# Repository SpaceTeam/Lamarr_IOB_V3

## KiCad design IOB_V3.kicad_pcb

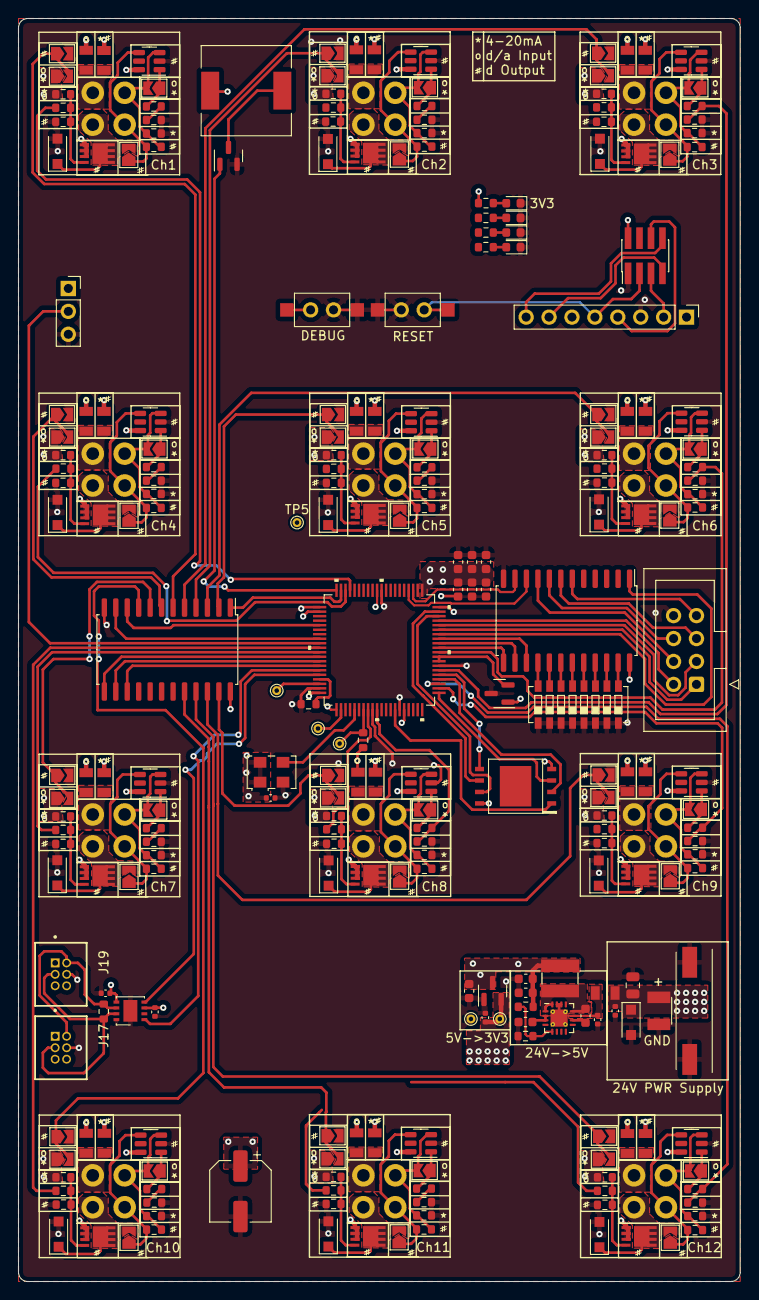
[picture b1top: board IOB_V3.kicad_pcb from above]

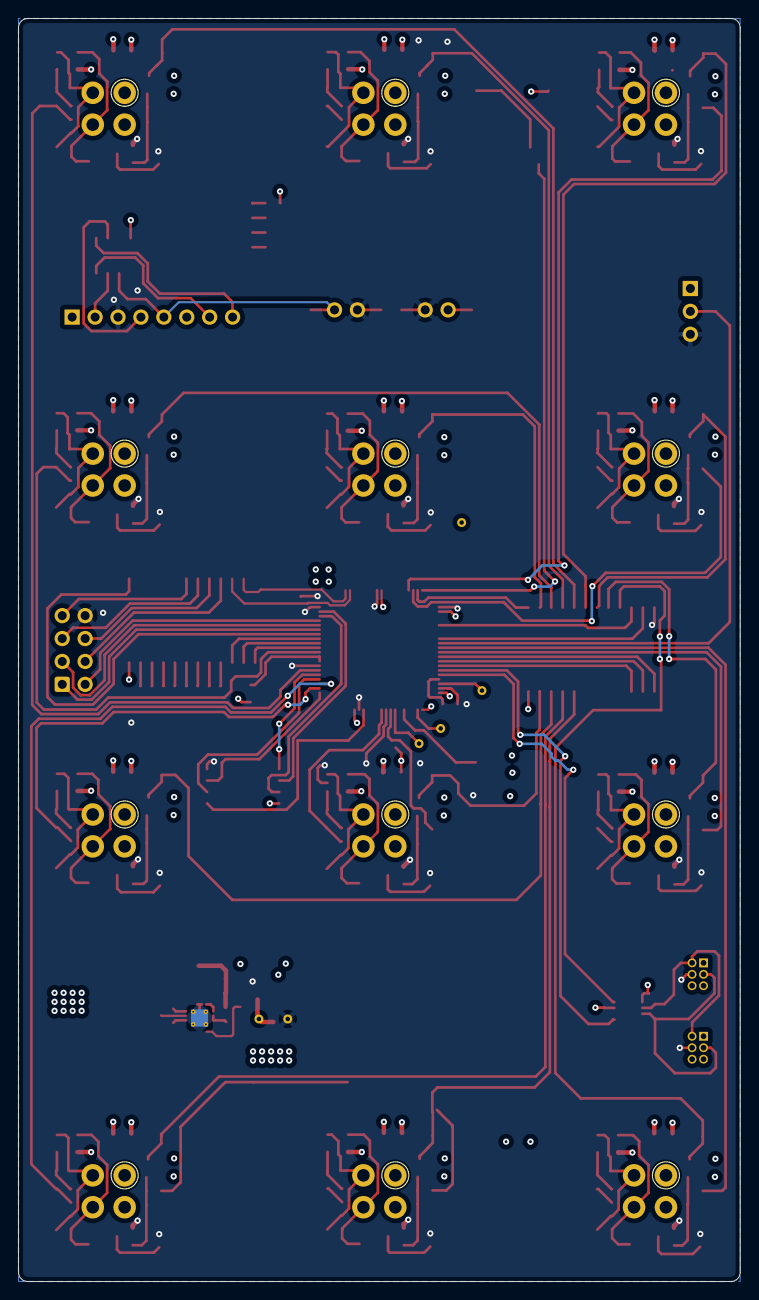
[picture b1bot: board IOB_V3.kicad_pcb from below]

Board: 4 copper layers, 80.0 x 140.0 mm, 266 parts (12 on the bottom side), 175 nets.

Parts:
C1, C3, C10, C11, C13, C15: 100n; C_0402_1005Metric
C2: 22u; C_0805_2012Metric
C4, C8: 10u; C_0603_1608Metric
C5, C9, C12, C16, C17, C18: 100n; C_0603_1608Metric
C6, C7: 22u; C_0603_1608Metric
C14: NP; CP_Elec_6.3x4.9
C19: 4.7u; C_0603_1608Metric
D1: 30V; D_SOD-123F
D2, D3, D4, D5, D6, D7, D8, D9, D10, D11, D12, D13: D; D_SOD-123F
D14, D15, D16, D17: LED; LED_0603_1608Metric
F1, F2, F3, F4, F5, F6, F7, F8, F9, F10, F11, F12, F13, F14, F15, F16, F17, F18, F19, F20, F21, F22, F23, F24, F25: Polyfuse; 0805L110SL PPTC Polyfuse Littelfuse
J1: Conn_01x02; Molex_MicroFit_2Pin_Vertical
J2: Conn_01x03; PinSocket_1x03_P2.54mm_Vertical
J3, J4, J5, J6, J7, J8, J9, J10, J11, J12, J13, J14: Conn_01x04; TE_M12_4_Pin_PCB
J15: Conn_01x08; PinHeader_1x08_P2.54mm_Vertical
J16: Conn_02x04_Odd_Even; PinHeader_2x04_P1.27mm_Vertical_SMD
J17, J19: TFC-103-01-F-D; SAMTEC_TFC-103-01-F-D
J18: Conn_01x08; IDC-Header_2x04_P2.54mm_Vertical
JP1, JP2, JP5, JP6, JP7, JP8, JP11, JP12, JP13, JP14, JP17, JP18, JP19, JP20, JP23, JP24, JP25, JP26, JP29, JP30, JP31, JP32, JP35, JP36, JP37, JP38, JP41, JP42, JP43, JP44, JP47, JP48, JP49, JP50, JP53, JP54, JP55, JP56, JP59, JP60, JP61, JP62, JP65, JP66, JP67, JP68, JP71, JP72: Jumper_2_Open; SolderJumper-2_P1.3mm_Open_TrianglePad1.0x1.5mm
L1: 4.7uH; SRN4018TA-4R7M
LS1: Speaker_Crystal; Piezo_Buzzer
Q1, Q2, Q3, Q4, Q5, Q6, Q7, Q8, Q9, Q10, Q11, Q12: BSZ0902NSATMA1; PG_TSDSON-8
Q13: SI2300; SOT-23
R1, R8, R15, R22, R29, R36, R43, R50, R57, R64, R71, R78, R93: 0R; R_0603_1608Metric
R2, R9, R16, R23, R30, R37, R44, R51, R58, R65, R72, R79: NP; R_0603_1608Metric
R3, R5, R10, R12, R17, R19, R24, R26, R31, R33, R38, R40, R45, R47, R52, R54, R59, R61, R66, R68, R73, R75, R80, R82, R85, R86: R; R_0603_1608Metric
R4, R11, R18, R25, R32, R39, R46, R53, R60, R67, R74, R81: Rgate; R_0603_1608Metric
R6, R7, R13, R14, R20, R21, R27, R28, R34, R35, R41, R42, R48, R49, R55, R56, R62, R63, R69, R70, R76, R77, R83, R84: Rpull; R_0603_1608Metric
R87, R88, R89, R90, R92: 120R; R_0603_1608Metric
R94: Rpullup; R_0603_1608Metric
SW1, SW2: SW_Push_Dual; SW_SPST_CK_RS282G05A3_and_THT
SW3: SW_DIP_x08; 8_Pin_DIP_Switch
TP1, TP2, TP3, TP4, TP5, TP6: TestPoint; TestPoint_THTPad_D1.0mm_Drill0.5mm
U1: REF3033; SOT-23
U2, U3, U4, U5, U6, U7, U8, U9, U10, U11, U12, U13: INA180; SOT-23-6
U14: TS30041; QFN-16-1EP_3x3mm_P0.5mm_EP1.9x1.9mm_ThermalVias
U15: MCP1700-3302E_SOT23; SOT-23
U16, U20: CD74HC4067M; SOIC-24W_7.5x15.4mm_P1.27mm
U17: MCP2562FD; DFN-8-1EP_3x3mm_P0.65mm_EP1.55x2.4mm
U18: W25Q256JV; WSON-8-8x6mm
U19: STM32G474MET3
X1: TXC-7C; Oscillator_SMD_TXC_7C-4Pin_5.0x3.2mm

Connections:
+3.3VA: U1.2 (OUT), U19.28 (VREF+), U19.29 (VDDA)
+3V3: C9.1, C10.1, C11.1, C12.1, C14.1, C15.1, C16.1, C17.1, C18.1, C19.1, F1.1, F3.1, F5.1, F7.1, F9.1, F11.1, F13.1, F15.1, F17.1, F19.1, F21.1, F23.1, J2.1, J15.1, J16.2, JP5.1 (A), JP11.1 (A), JP17.1 (A), JP23.1 (A), JP29.1 (A), JP35.1 (A), JP41.1 (A), JP47.1 (A), JP53.1 (A), JP59.1 (A), JP65.1 (A), JP71.1 (A), LS1.1, R6.1, R13.1, R20.1, R27.1, R34.1, R41.1, R48.1, R55.1, R62.1, R69.1, R76.1, R83.1, R87.1, R94.1, TP3.1, U2.6 (V+), U3.6 (V+), U4.6 (V+), U5.6 (V+), U6.6 (V+), U7.6 (V+), U8.6 (V+), U9.6 (V+), U10.6 (V+), U11.6 (V+), U12.6 (V+), U13.6 (V+), U15.2 (VO), U17.5 (Vio), U18.8 (VCC), U19.1 (VBAT), U19.16 (VDD), U19.41 (VDD), U19.51 (VDD), U19.62 (VDD), U19.80 (VDD), X1.1 (EN), X1.4 (Vdd)
+5V: C6.2, C7.2, C8.1, C13.2, J17.01, J19.01, L1.2, R85.2, U1.1 (IN), U15.3 (VI), U16.24 (VCC), U17.3 (VDD), U20.24 (VCC)
+24V: C1.1, C2.1, D1.1 (A1), F2.1, F4.1, F6.1, F8.1, F10.1, F12.1, F14.1, F16.1, F18.1, F20.1, F22.1, F24.1, F25.1, J1.1
/En1: R4.1, U19.57 (PA9)
/En2: R11.1, U19.56 (PA8)
/En3: R18.1, U19.46 (PB15)
/En4: R25.1, U19.58 (PA10)
/En5: R32.1, U19.11 (PC3)
/En6: R39.1, U19.52 (PC6)
/En7: R46.1, U19.71 (PD2)
/En8: R53.1, U19.8 (PC0)
/En9: R60.1, U19.9 (PC1)
/En10: R67.1, U19.70 (PD1)
/En11: R74.1, U19.54 (PC8)
/En12: R81.1, U19.55 (PC9)
/MCU/ADC1_IN1: R1.2, R2.1, U19.12 (PA0)
/MCU/ADC1_IN2: R8.2, R9.1, U19.13 (PA1)
/MCU/ADC1_IN4: R29.2, R30.1, U19.17 (PA3)
/MCU/ADC1_IN5: R22.2, R23.1, U19.45 (PB14)
/MCU/ADC1_IN8: R50.2, R51.1, U19.10 (PC2)
/MCU/ADC1_IN14: R43.2, R44.1, U19.42 (PB11)
/MCU/ADC2_IN3: R64.2, R65.1, U19.20 (PA6)
/MCU/ADC2_IN5: R57.2, R58.1, U19.22 (PC4)
/MCU/ADC2_IN11: R78.2, R79.1, U19.23 (PC5)
/MCU/ADC2_IN12: R15.2, R16.1, U19.26 (PB2)
/MCU/ADC3_IN4: R36.2, R37.1, U19.30 (PE7)
/MCU/ADC3_IN7: R71.2, R72.1, U19.49 (PD10)
/MCU/BUTTON_1: SW2.2, U19.53 (PC7)
/MCU/CAN1_RX: U17.4 (RXD), U19.76 (PB7)
/MCU/CAN1_TX: U17.1 (TXD), U19.75 (PB6)
/MCU/CANH1: J17.03, J19.03, R92.1, U17.7 (CANH)
/MCU/CANL1: J17.02, J19.02, R92.2, U17.6 (CANL)
/MCU/CLK: U19.5 (PF0-OSC_IN), X1.3 (OUT)
/MCU/DEBUG_LED: R90.1, U19.19 (PA5)
/MCU/INPUT_SELECT: U19.59 (PA11), U20.1 (COM)
/MCU/MUX1_SEL0: U16.10 (S0), U19.44 (PB13)
/MCU/MUX1_SEL1: U16.11 (S1), U19.43 (PB12)
/MCU/MUX1_SEL2: U16.14 (S2), U19.32 (PE9)
/MCU/MUX1_SEL3: U16.13 (S3), U19.31 (PE8)
/MCU/MUX1_~EN: U16.15 (~E), U19.33 (PE10)
/MCU/MUX2_SEL0: U19.65 (PA15), U20.10 (S0)
/MCU/MUX2_SEL1: U19.68 (PC12), U20.11 (S1)
/MCU/MUX2_SEL2: U19.73 (PB4), U20.14 (S2)
/MCU/MUX2_SEL3: U19.72 (PB3), U20.13 (S3)
/MCU/MUX2_~EN: U19.74 (PB5), U20.15 (~E)
/MCU/NRST: J15.5, J16.3, R94.2, SW1.2, TP2.1, U19.7 (PG10-NRST)
/MCU/QUADSPI1_BK1_IO0: U18.5 (DI(IO0)), U19.25 (PB1)
/MCU/QUADSPI1_BK1_IO1: U18.2 (DO(IO1)), U19.24 (PB0)
/MCU/QUADSPI1_BK1_IO2: U18.3 (~WP(IO2)), U19.21 (PA7)
/MCU/QUADSPI1_BK1_IO3: U18.7 (~RESET(IO3)), U19.38 (PE15)
/MCU/QUADSPI1_BK1_NCS: U18.1 (~CS), U19.14 (PA2)
/MCU/QUADSPI1_CLK: U18.6 (CLK), U19.39 (PB10)
/MCU/SPI4_MISO: J18.3, U19.36 (PE13)
/MCU/SPI4_MOSI: J18.2, U19.37 (PE14)
/MCU/SPI4_NSS: U16.1 (COM), U19.34 (PE11)
/MCU/SPI4_NSS1: J18.4, U16.9 (I0)
/MCU/SPI4_NSS2: J18.5, U16.7 (I2)
/MCU/SPI4_NSS3: J18.6, U16.8 (I1)
/MCU/SPI4_NSS4: J18.7, U16.6 (I3)
/MCU/SPI4_SCK: J18.1, U19.35 (PE12)
/MCU/STATUS_LED_1: R88.1, U19.47 (PD8)
/MCU/STATUS_LED_2: R89.1, U19.48 (PD9)
/MCU/SWCLK: J15.2, J16.5, U19.64 (PA14)
/MCU/SWDIO: J15.4, J16.6, U19.63 (PA13)
/MCU/Speaker_1: Q13.1 (G), U19.60 (PA12)
/MCU/UART4_RX: J15.8, J16.8, U19.67 (PC11)
/MCU/UART4_TX: J15.7, J16.7, U19.66 (PC10)
/OneWire: J2.2, U19.69 (PD0)
/Select1: JP5.2 (B), JP6.1 (A), U20.6 (I3)
/Select2: JP11.2 (B), JP12.1 (A), U20.4 (I5)
/Select3: JP17.2 (B), JP18.1 (A), U20.5 (I4)
/Select4: JP23.2 (B), JP24.1 (A), U20.7 (I2)
/Select5: JP29.2 (B), JP30.1 (A), U20.2 (I7)
/Select6: JP35.2 (B), JP36.1 (A), U20.3 (I6)
/Select7: JP41.2 (B), JP42.1 (A), U20.8 (I1)
/Select8: JP47.2 (B), JP48.1 (A), U20.23 (I8)
/Select9: JP53.2 (B), JP54.1 (A), U20.22 (I9)
/Select10: JP59.2 (B), JP60.1 (A), U20.9 (I0)
/Select11: JP65.2 (B), JP66.1 (A), U20.20 (I11)
/Select12: JP71.2 (B), JP72.1 (A), U20.21 (I10)
GND: C1.2, C2.2, C3.1, C4.1, C6.1, C7.1, C8.2, C9.2, C10.2, C11.2, C12.2, C13.1, C14.2, C15.2, C16.2, C17.2, C18.2, C19.2, D1.2 (A2), D2.2 (A), D3.2 (A), D4.2 (A), D5.2 (A), D6.2 (A), D7.2 (A), D8.2 (A), D9.2 (A), D10.2 (A), D11.2 (A), D12.2 (A), D13.2 (A), D14.1 (K), D15.1 (K), D16.1 (K), D17.1 (K), J1.2, J1.MP (MountPin), J2.3, J15.3, J16.1, J17.04, J18.8, J19.04, JP6.2 (B), JP12.2 (B), JP18.2 (B), JP24.2 (B), JP30.2 (B), JP36.2 (B), JP42.2 (B), JP48.2 (B), JP54.2 (B), JP60.2 (B), JP66.2 (B), JP72.2 (B), Q1.1 (S), Q2.1 (S), Q3.1 (S), Q4.1 (S), Q5.1 (S), Q6.1 (S), Q7.1 (S), Q8.1 (S), Q9.1 (S), Q10.1 (S), Q11.1 (S), Q12.1 (S), Q13.2 (S), R2.2, R3.2, R7.2, R9.2, R10.2, R14.2, R16.2, R17.2, R21.2, R23.2, R24.2, R28.2, R30.2, R31.2, R35.2, R37.2, R38.2, R42.2, R44.2, R45.2, R49.2, R51.2, R52.2, R56.2, R58.2, R59.2, R63.2, R65.2, R66.2, R70.2, R72.2, R73.2, R77.2, R79.2, R80.2, R84.2, R86.2, R93.1, SW1.1, SW2.1, SW3.1, SW3.2, SW3.3, SW3.4, SW3.5, SW3.6, SW3.7, SW3.8, TP1.1, U1.3 (GND), U2.2 (GND), U3.2 (GND), U4.2 (GND), U5.2 (GND), U6.2 (GND), U7.2 (GND), U8.2 (GND), U9.2 (GND), U10.2 (GND), U11.2 (GND), U12.2 (GND), U13.2 (GND), U14.4 (GND), U14.14 (PGND), U14.15 (PGND), U14.17 (PAD), U15.1 (GND), U16.12 (GND), U17.2 (VSS), U17.8 (SHDN), U17.9 (PAD), U18.4 (GND), U19.15 (VSS), U19.27 (VSSA), U19.40 (VSS), U19.50 (VSS), U19.61 (VSS), U19.79 (VSS), U20.12 (GND), X1.2 (GND)
unnamed: C3.2, C4.2, F25.2, U14.2 (VCC), U14.3 (VCC), U14.11 (VCC)
unnamed: C5.1, L1.1, U14.1 (VSW), U14.12 (VSW), U14.13 (VSW), U14.16 (VSW)
unnamed: C5.2, U14.10 (BST)
unnamed: D2.1 (K), J3.4, JP2.2 (B), Q1.3 (D)
unnamed: D3.1 (K), J4.4, JP8.2 (B), Q2.3 (D)
unnamed: D4.1 (K), J5.4, JP14.2 (B), Q3.3 (D)
unnamed: D5.1 (K), J6.4, JP20.2 (B), Q4.3 (D)
unnamed: D6.1 (K), J7.4, JP26.2 (B), Q5.3 (D)
unnamed: D7.1 (K), J8.4, JP32.2 (B), Q6.3 (D)
unnamed: D8.1 (K), J9.4, JP38.2 (B), Q7.3 (D)
unnamed: D9.1 (K), J10.4, JP44.2 (B), Q8.3 (D)
unnamed: D10.1 (K), J11.4, JP50.2 (B), Q9.3 (D)
unnamed: D11.1 (K), J12.4, JP56.2 (B), Q10.3 (D)
unnamed: D12.1 (K), J13.4, JP62.2 (B), Q11.3 (D)
unnamed: D13.1 (K), J14.4, JP68.2 (B), Q12.3 (D)
unnamed: D14.2 (A), R87.2
unnamed: D15.2 (A), R88.2
unnamed: D16.2 (A), R89.2
unnamed: D17.2 (A), R90.2
unnamed: F1.2, F2.2, J3.1
unnamed: F3.2, F4.2, J4.1
unnamed: F5.2, F6.2, J5.1
unnamed: F7.2, F8.2, J6.1
unnamed: F9.2, F10.2, J7.1
unnamed: F11.2, F12.2, J8.1
unnamed: F13.2, F14.2, J9.1
unnamed: F15.2, F16.2, J10.1
unnamed: F17.2, F18.2, J11.1
unnamed: F19.2, F20.2, J12.1
unnamed: F21.2, F22.2, J13.1
unnamed: F23.2, F24.2, J14.1
unnamed: J3.2, JP1.2 (B), R3.1, R5.1, U2.3 (+)
unnamed: J3.3, JP2.1 (A), R5.2, U2.4 (-)
unnamed: J4.2, JP7.2 (B), R10.1, R12.1, U3.3 (+)
unnamed: J4.3, JP8.1 (A), R12.2, U3.4 (-)
unnamed: J5.2, JP13.2 (B), R17.1, R19.1, U4.3 (+)
unnamed: J5.3, JP14.1 (A), R19.2, U4.4 (-)
unnamed: J6.2, JP19.2 (B), R24.1, R26.1, U5.3 (+)
unnamed: J6.3, JP20.1 (A), R26.2, U5.4 (-)
unnamed: J7.2, JP25.2 (B), R31.1, R33.1, U6.3 (+)
unnamed: J7.3, JP26.1 (A), R33.2, U6.4 (-)
unnamed: J8.2, JP31.2 (B), R38.1, R40.1, U7.3 (+)
unnamed: J8.3, JP32.1 (A), R40.2, U7.4 (-)
unnamed: J9.2, JP37.2 (B), R45.1, R47.1, U8.3 (+)
unnamed: J9.3, JP38.1 (A), R47.2, U8.4 (-)
unnamed: J10.2, JP43.2 (B), R52.1, R54.1, U9.3 (+)
unnamed: J10.3, JP44.1 (A), R54.2, U9.4 (-)
unnamed: J11.2, JP49.2 (B), R59.1, R61.1, U10.3 (+)
unnamed: J11.3, JP50.1 (A), R61.2, U10.4 (-)
unnamed: J12.2, JP55.2 (B), R66.1, R68.1, U11.3 (+)
unnamed: J12.3, JP56.1 (A), R68.2, U11.4 (-)
unnamed: J13.2, JP61.2 (B), R73.1, R75.1, U12.3 (+)
unnamed: J13.3, JP62.1 (A), R75.2, U12.4 (-)
unnamed: J14.2, JP67.2 (B), R80.1, R82.1, U13.3 (+)
unnamed: J14.3, JP68.1 (A), R82.2, U13.4 (-)
unnamed: JP1.1 (A), R1.1, U2.1
unnamed: JP7.1 (A), R8.1, U3.1
unnamed: JP13.1 (A), R15.1, U4.1
unnamed: JP19.1 (A), R22.1, U5.1
unnamed: JP25.1 (A), R29.1, U6.1
unnamed: JP31.1 (A), R36.1, U7.1
unnamed: JP37.1 (A), R43.1, U8.1
unnamed: JP43.1 (A), R50.1, U9.1
unnamed: JP49.1 (A), R57.1, U10.1
unnamed: JP55.1 (A), R64.1, U11.1
unnamed: JP61.1 (A), R71.1, U12.1
unnamed: JP67.1 (A), R78.1, U13.1
unnamed: LS1.2, Q13.3 (D)
unnamed: Q1.2 (G), R4.2, R6.2, R7.1
unnamed: Q2.2 (G), R11.2, R13.2, R14.1
unnamed: Q3.2 (G), R18.2, R20.2, R21.1
unnamed: Q4.2 (G), R25.2, R27.2, R28.1
unnamed: Q5.2 (G), R32.2, R34.2, R35.1
unnamed: Q6.2 (G), R39.2, R41.2, R42.1
unnamed: Q7.2 (G), R46.2, R48.2, R49.1
unnamed: Q8.2 (G), R53.2, R55.2, R56.1
unnamed: Q9.2 (G), R60.2, R62.2, R63.1
unnamed: Q10.2 (G), R67.2, R69.2, R70.1
unnamed: Q11.2 (G), R74.2, R76.2, R77.1
unnamed: Q12.2 (G), R81.2, R83.2, R84.1
unnamed: R85.1, R86.1, U14.5 (FB)
unnamed: R93.2, U19.77 (PB8-BOOT0)
unnamed: SW3.9, U16.23 (I8)
unnamed: SW3.10, U16.22 (I9)
unnamed: SW3.11, U16.21 (I10)
unnamed: SW3.12, U16.20 (I11)
unnamed: SW3.13, U16.19 (I12)
unnamed: SW3.14, U16.18 (I13)
unnamed: SW3.15, U16.17 (I14)
unnamed: SW3.16, U16.16 (I15)
unnamed: TP4.1, U19.78 (PB9)
unnamed: TP6.1, U19.2 (PC13)
unnamed: TP5.1, U19.18 (PA4)

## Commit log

2022-11-19 Initial changes made
    WIP on this iteration
2022-11-22 Question for @georg
    Was kann man genau entfernen?
2022-11-27 WIP
    for @Markus
2022-11-29 Schematic nearly complete
2022-11-29 Schematic ready for crosscheck
2022-11-29 Speaker changed to MOSFET circuit
2022-11-30 Routing begin
2022-11-30 Routing WIP
2022-12-01 Connection layout set
2022-12-02 Layout WIP
2022-12-05 Connectors change and part side flip
2022-12-05 Connectors routed
2022-12-06 Routing basics done
    All layers + the basic layout is already set
2022-12-12 Routing complete. Stitching missing
2022-12-13 Added 2nd SPI4 connector
2022-12-13 Ready for first review
2022-12-23 5V SMPS Layout Edit
    The 5V SMPS Layout was changed to a similar one as in the IOB V2
2022-12-24 Added different Can connector
    Used T1M-04-F-SV-L as a can connector
2022-12-30 100n capacitor position change
2023-01-04 Layer change + INA change + SPI 24V added + minor changes
    Stitching is still missing
2023-01-05 All GNDD and GNDA changed to GND
2023-01-05 Stitching complete
2023-01-06 Added JP for GS + Cap @STM Pin 1
2023-01-07 Changed 5V Plane to 3.3V Changed INA350 Supply to 3.3V Minor tweaks
2023-01-07 Intermediate step for fixing Lib problems
2023-01-07 Added Submodule for Lib
2023-01-07 Fixed Lib Mess
2023-01-07 Added Gerber Files

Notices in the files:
parts and their libraries:
Copyright 2021 Accelerated Designs. All rights reserved.
